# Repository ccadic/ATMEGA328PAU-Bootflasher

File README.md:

# ATMEGA328PAU-Bootflasher
Small PCB to flash the bootloader on a 328P-AU

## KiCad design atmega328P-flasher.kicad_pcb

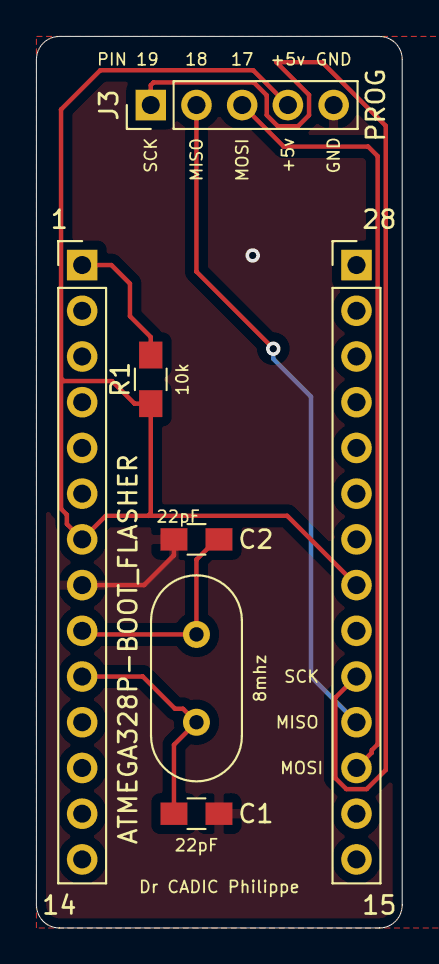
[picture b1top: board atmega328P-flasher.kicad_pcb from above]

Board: 2 copper layers, 20.3 x 49.5 mm, 7 parts (0 on the bottom side), 8 nets.

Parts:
C1, C2: 22pF; C_0805_HandSoldering
J1: Conn_01x14_Female; Socket_Strip_Straight_1x14_Pitch2.54mm
J2: Conn_01x14_Female6RevNumb; Socket_Strip_Straight_1x14_Pitch2.54mmREV
J3: PROG; Socket_Strip_Straight_1x05_Pitch2.54mm
R1: 10k; R_0805_HandSoldering
Y1: 8mhz; Crystal_HC49-4H_Vertical

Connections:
+5V: J1.7, J2.21, J3.4, R1.1
GND: C1.2, C2.2, J1.8, J2.22, J3.5
unnamed: C1.1, J1.10, Y1.1
unnamed: C2.1, J1.9, Y1.2
unnamed: J1.1, R1.2
unnamed: J2.17, J3.3
unnamed: J2.18, J3.2
unnamed: J2.19, J3.1
